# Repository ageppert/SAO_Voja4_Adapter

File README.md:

# SAO VOJA4 BADGE ADAPTER

Hardware add-on to enable Voja4 to speak I2C with a full-featured 6-pin SAO socket.

Maybe even SPI!

Follow this project at: https://hackaday.io/project/198394-sao-adapter-for-voja4-badge

Hardware Version 1.0 Prototype

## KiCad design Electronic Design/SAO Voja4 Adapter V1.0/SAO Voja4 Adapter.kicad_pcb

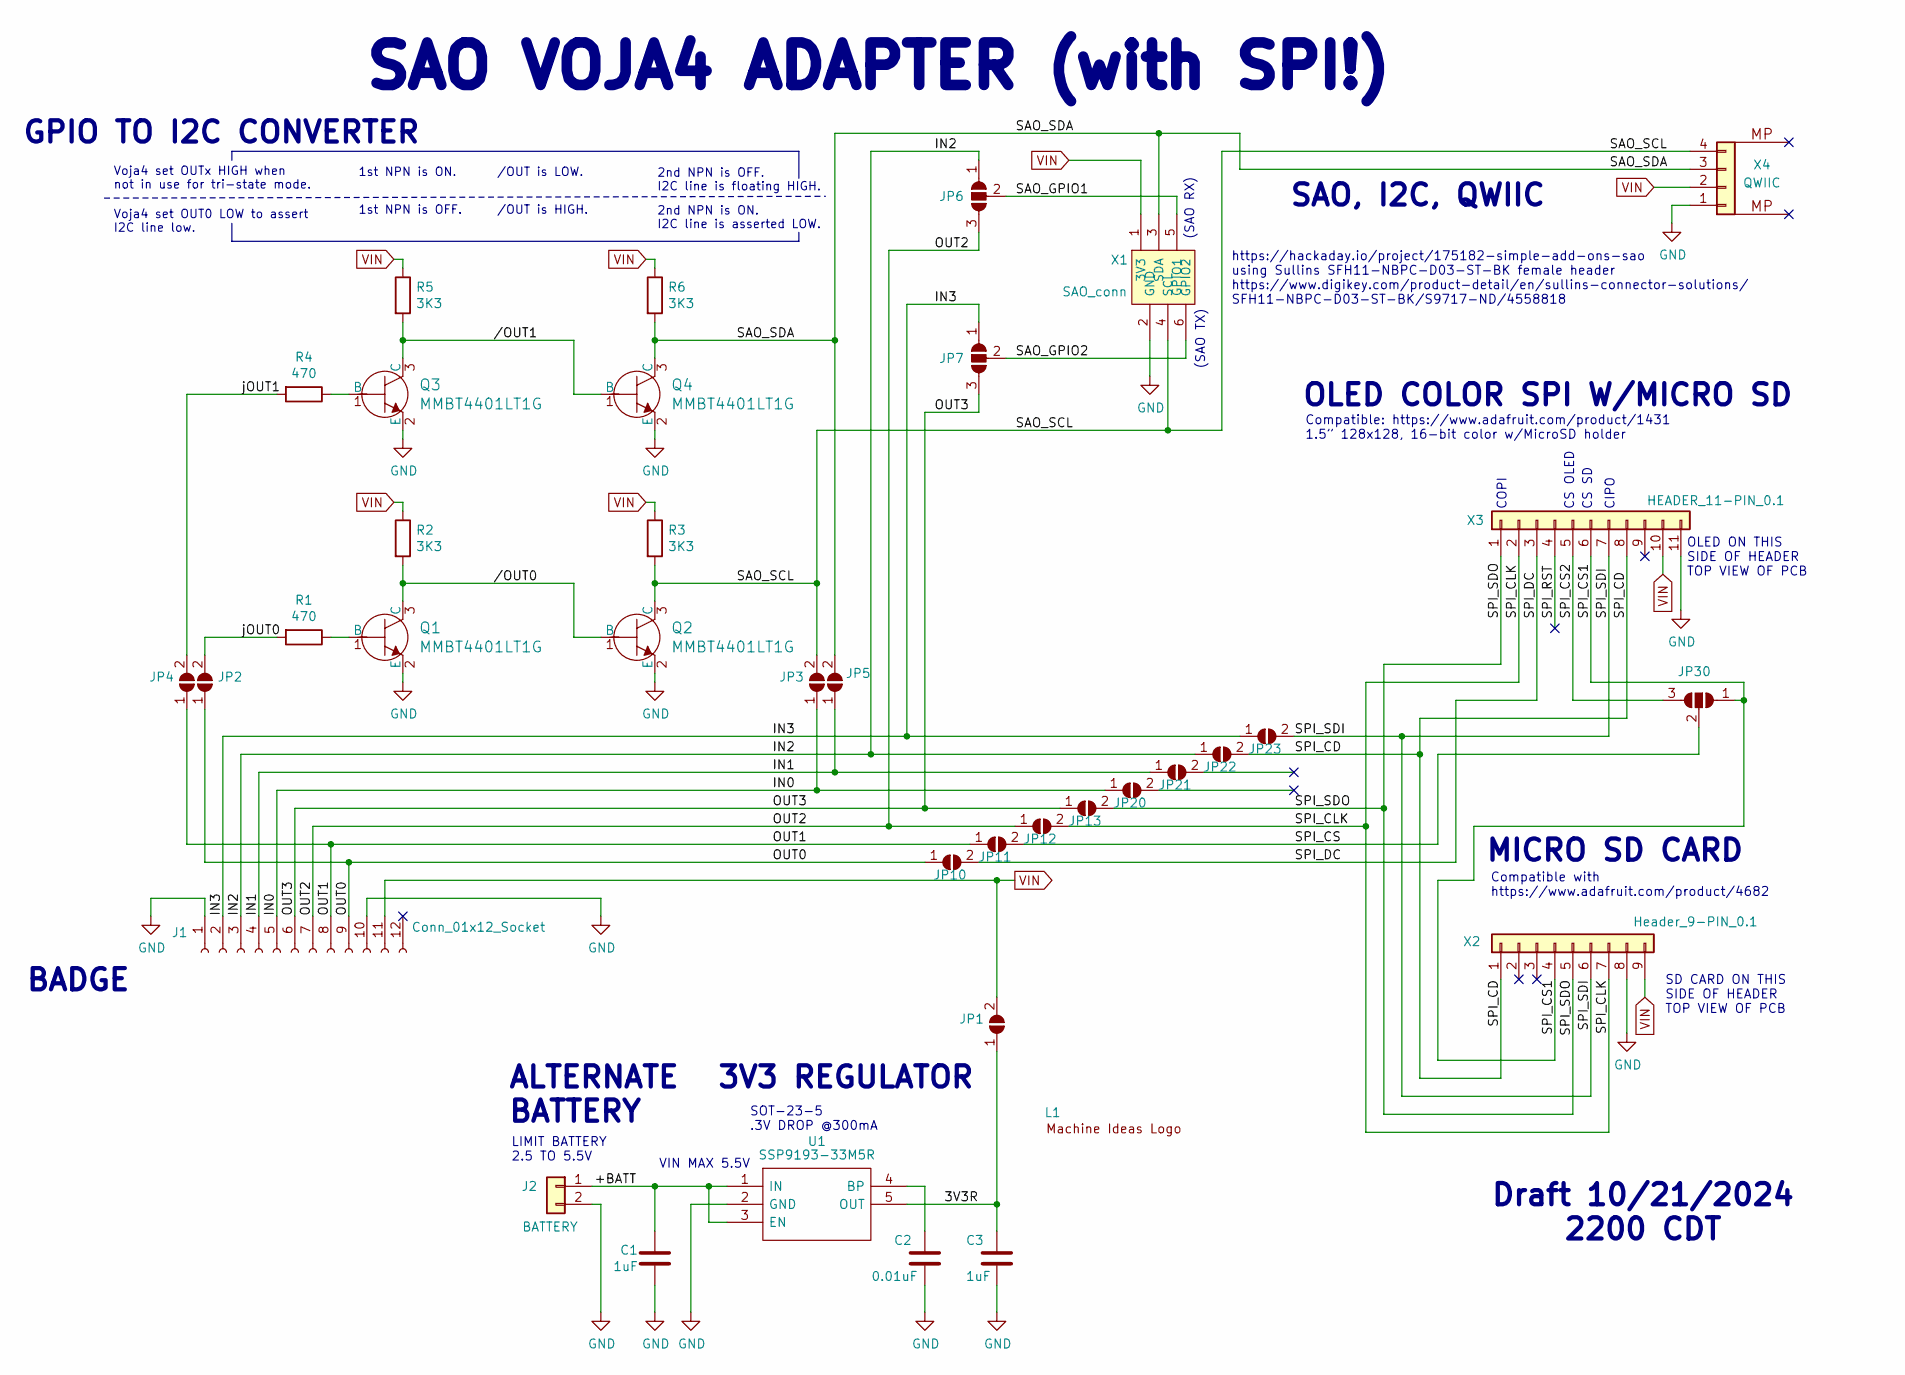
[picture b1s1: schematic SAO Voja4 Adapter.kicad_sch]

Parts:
C1, C3: 1uF; C_0805_2012Metric; LCSC C28323
C2: 0.01uF; C_0805_2012Metric; LCSC C1710
J1: Conn_01x12_Socket; PinSocket_1x12_P2.54mm_Horizontal
J2: BATTERY; PinSocket_1x02_P2.54mm_Vertical
JP1: VSEL; SolderJumper-2_P1.3mm_Open_RoundedPad1.0x1.5mm
JP2, JP3, JP4, JP5, JP10, JP11, JP12, JP13, JP20, JP21, JP22, JP23: JP; SolderJumper-2_P1.3mm_Open_RoundedPad1.0x1.5mm
JP6, JP7, JP30: SolderJumper_3_Open; SolderJumper-3_P1.3mm_Open_RoundedPad1.0x1.5mm_NumberLabels
L1: Machine_Ideas_logo
Q1, Q2, Q3, Q4: MMBT4401LT1G; SOT-23-3; MPN MMBT4401LT1G; Digi-Key_PN MMBT4401LT1GOSCT-ND
R1, R4: 470; R_0805_2012Metric; LCSC C17710
R2, R3, R5, R6: 3K3; R_0805_2012Metric; LCSC C17398
U1: SSP9193-33M5R; SOT-23-5; Manufacturer_Part_Number SGM2007-3.3XN5/TR; Mouser Part Number SGM2007-3.3XN5/TR
X1: SAO_conn; Badgelife-SAOv169-BADGE-2x3-no-front-text; MPN SFH11-NBPC-D03-ST-BK
X2: Header_9-PIN_0.1; PinSocket_1x09_P2.54mm_Vertical
X3: HEADER_11-PIN_0.1; PinSocket_1x11_P2.54mm_Vertical
X4: QWIIC; JST_SH_SM04B-SRSS-TB_1x04-1MP_P1.00mm_Horizontal; MPN SM04B-SRSS-TB; LCSC C160404

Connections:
/3V3R: C3.1, JP1.1 (A), U1.5 (OUT)
/+BATT: C1.1, J2.1, U1.1 (IN), U1.3 (EN)
/IN0: J1.5, JP3.1 (A), JP20.1 (A)
/IN1: J1.4, JP5.1 (A), JP21.1 (A)
/IN2: J1.3, JP6.1 (A), JP22.1 (A)
/IN3: J1.2, JP7.1 (A), JP23.1 (A)
/OUT0: J1.9, JP2.1 (A), JP10.1 (A)
/OUT1: J1.8, JP4.1 (A), JP11.1 (A)
/OUT2: J1.7, JP6.3 (B), JP12.1 (A)
/OUT3: J1.6, JP7.3 (B), JP13.1 (A)
/SAO_GPIO1: JP6.2 (C), X1.5 (GPIO1)
/SAO_GPIO2: JP7.2 (C), X1.6 (GPIO2)
/SAO_SCL: JP3.2 (B), Q2.3 (C), R3.2, X1.4 (SCL), X4.4
/SAO_SDA: JP5.2 (B), Q4.3 (C), R6.2, X1.3 (SDA), X4.3
/SPI_CD: JP22.2 (B), X2.1, X3.8
/SPI_CLK: JP12.2 (B), X2.7, X3.2
/SPI_CS: JP11.2 (B), JP30.2 (C)
/SPI_CS1: JP30.1 (A), X2.4, X3.6
/SPI_CS2: JP30.3 (B), X3.5
/SPI_DC: JP10.2 (B), X3.3
/SPI_RST: X3.4
/SPI_SDI: JP23.2 (B), X2.6, X3.7
/SPI_SDO: JP13.2 (B), X2.5, X3.1
/jOUT0: JP2.2 (B), R1.2
/jOUT1: JP4.2 (B), R4.2
//OUT0: Q1.3 (C), Q2.1 (B), R2.2
//OUT1: Q3.3 (C), Q4.1 (B), R5.2
GND: C1.2, C2.2, C3.2, J1.1, J1.10, J2.2, Q1.2 (E), Q2.2 (E), Q3.2 (E), Q4.2 (E), U1.2 (GND), X1.2 (GND), X2.8, X3.11, X4.1
unnamed: Q1.1 (B), R1.1
unnamed: Q3.1 (B), R4.1
unnamed: C2.1, U1.4 (BP)
VIN: J1.11, JP1.2 (B), R2.1, R3.1, R5.1, R6.1, X1.1 (3V3), X2.9, X3.10, X4.2

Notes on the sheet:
https://hackaday.io/project/175182-simple-add-ons-sao using Sullins SFH11-NBPC-D03-ST-BK female header https://www.digikey.com/product-detail/en/sullins-connector-solutions/ SFH11-NBPC-D03-ST-BK/S9717-ND/4558818
COPI
CS SD
2nd NPN is ON. I2C line is asserted LOW.
Draft 10/21/2024 2200 CDT
3V3 REGULATOR
Compatible with https://www.adafruit.com/product/4682
GPIO TO I2C CONVERTER
Voja4 set OUTx HIGH when not in use for tri-state mode.
SAO VOJA4 ADAPTER (with SPI!)
CS OLED
Voja4 set OUT0 LOW to assert I2C line low.
MICRO SD CARD
SOT-23-5 .3V DROP @300mA
OLED ON THIS SIDE OF HEADER TOP VIEW OF PCB
2nd NPN is OFF. I2C line is floating HIGH.
Compatible: https://www.adafruit.com/product/1431 1.5” 128x128, 16-bit color w/MicroSD holder
ALTERNATE BATTERY
(SAO TX)
1st NPN is ON.
VIN MAX 5.5V
1st NPN is OFF.
BADGE
OLED COLOR SPI W/MICRO SD
SAO, I2C, QWIIC
SD CARD ON THIS SIDE OF HEADER TOP VIEW OF PCB
CIPO
/OUT is HIGH.
/OUT is LOW.
LIMIT BATTERY 2.5 TO 5.5V
(SAO RX)

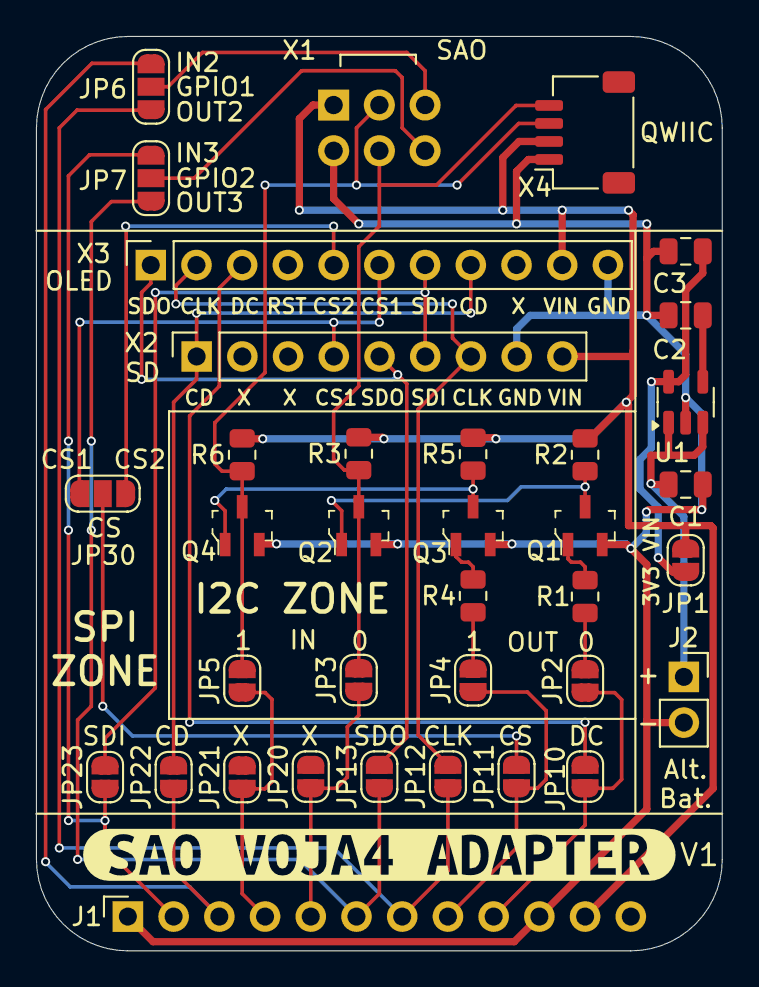
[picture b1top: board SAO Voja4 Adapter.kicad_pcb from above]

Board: 2 copper layers, 38.1 x 50.8 mm, 38 parts (1 on the bottom side), 31 nets.

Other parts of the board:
kibuzzard-671724A5: G***; kibuzzard-671724A5

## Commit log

2024-10-22 First draft
    FIRST DRAFT FOR REVIEW!!!
2024-10-22 Add more images
2024-10-23 Released V1 boards
2024-10-23 Remove draft V1 schematic
2024-10-23 Update readme image
2024-10-23 fix render filename
2024-10-23 And SPI
2024-10-23 Add BOM items in KiCAD schematic
2026-06-01 Add documentation notes and schematic configs
2026-06-01 Add Koppany's demo firmware
2026-06-01 Add real proto pic
